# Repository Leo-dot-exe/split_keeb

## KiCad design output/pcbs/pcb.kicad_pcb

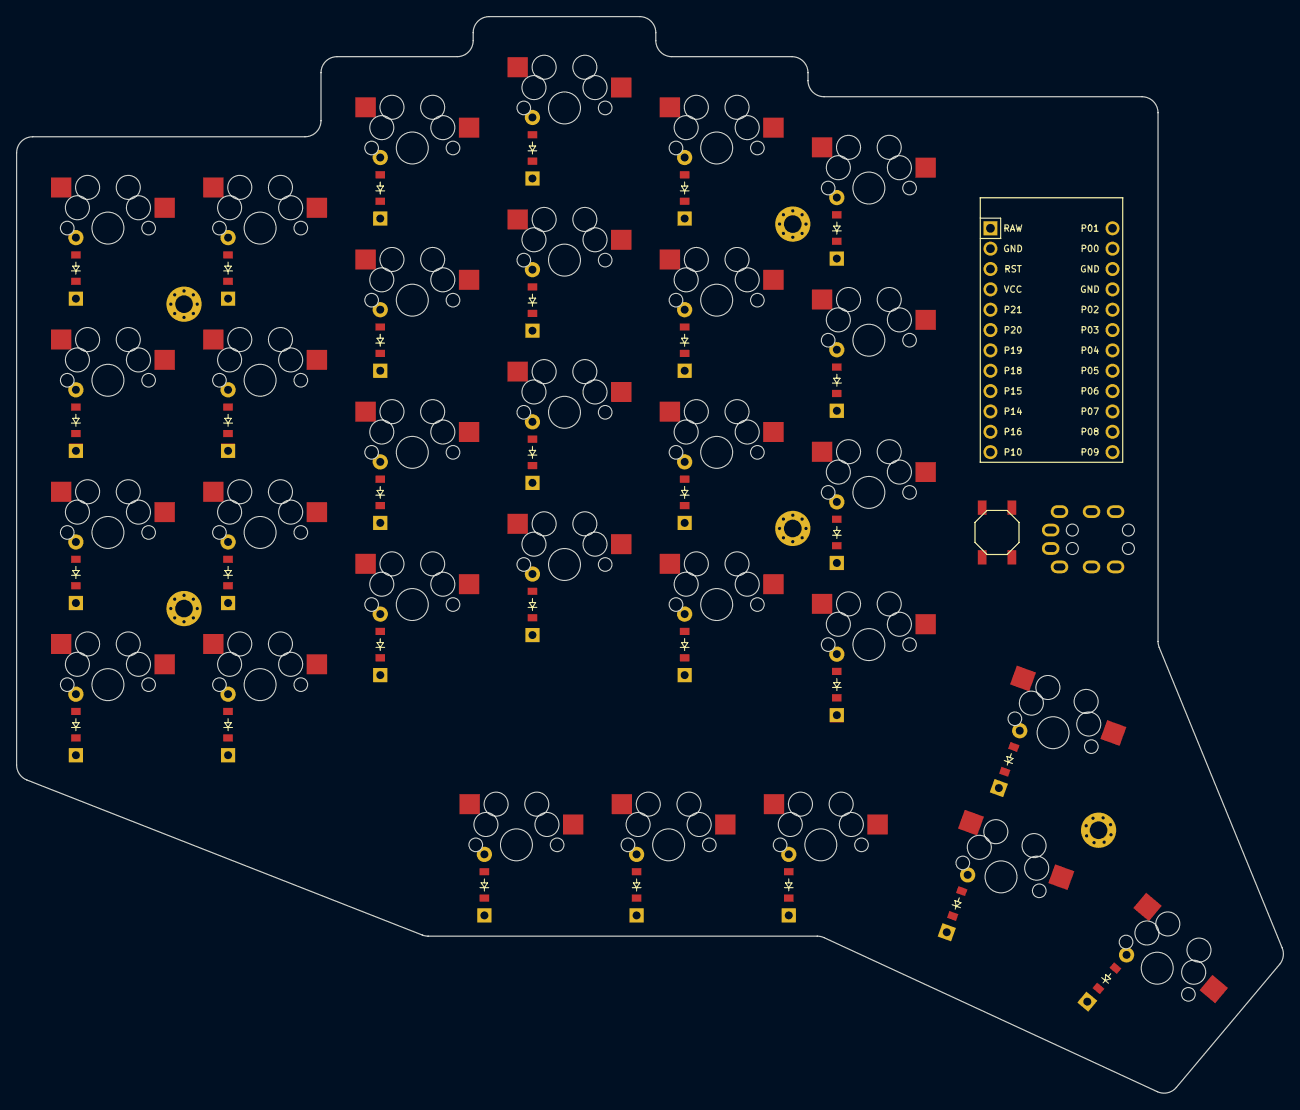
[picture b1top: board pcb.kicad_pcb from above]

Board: 2 copper layers, 158.2 x 134.4 mm, 68 parts (0 on the bottom side), 46 nets, no tracks yet.

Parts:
B1: SW_TACT_ALPS_SKQGABE010
D1, D2, D3, D4, D5, D6, D7, D8, D9, D10, D11, D12, D13, D14, D15, D16, D17, D18, D19, D20, D21, D22, D23, D24, D25, D26, D27, D28, D29, D30: ComboDiode
MCU1: ProMicro
S1, S2, S3, S4, S5, S6, S7, S8, S9, S10, S11, S12, S13, S14, S15, S16, S17, S18, S19, S20, S21, S22, S23, S24, S25, S26, S27, S28, S29, S30: MX
TRRS1: TRRS-PJ-320A-dual
_1, _2, _3, _4, _5: MountingHole_2.2mm_M2_Pad_Via

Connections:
GND: B1.1, MCU1.2, MCU1.15, MCU1.16, TRRS1.1
P0: MCU1.14, TRRS1.3
P1: MCU1.13, TRRS1.4
P7: MCU1.22, S21.1, S22.1, S23.1, S24.1, S30.1
P8: MCU1.23, S17.1, S18.1, S19.1, S20.1, S29.1
P9: MCU1.24, S13.1, S14.1, S15.1, S16.1, S28.1
P10: MCU1.12, S9.1, S10.1, S11.1, S12.1, S27.1
P14: MCU1.10, S1.1, S2.1, S3.1, S4.1, S25.1
P15: D25.1, D26.1, D27.1, D28.1, D29.1, D30.1, MCU1.9
P16: MCU1.11, S5.1, S6.1, S7.1, S8.1, S26.1
P18: D1.1, D5.1, D9.1, D13.1, D17.1, D21.1, MCU1.8
P19: D2.1, D6.1, D10.1, D14.1, D18.1, D22.1, MCU1.7
P20: D3.1, D7.1, D11.1, D15.1, D19.1, D23.1, MCU1.6
P21: D4.1, D8.1, D12.1, D16.1, D20.1, D24.1, MCU1.5
RST: B1.2, MCU1.3
VCC: MCU1.4, TRRS1.2
index_bottom: D17.2, S17.2
index_home: D18.2, S18.2
index_num: D20.2, S20.2
index_top: D19.2, S19.2
inner_bottom: D21.2, S21.2
inner_home: D22.2, S22.2
inner_num: D24.2, S24.2
inner_top: D23.2, S23.2
middle_bottom: D13.2, S13.2
middle_home: D14.2, S14.2
middle_num: D16.2, S16.2
middle_top: D15.2, S15.2
outer_bottom: D1.2, S1.2
outer_home: D2.2, S2.2
outer_num: D4.2, S4.2
outer_top: D3.2, S3.2
pinky_bottom: D5.2, S5.2
pinky_home: D6.2, S6.2
pinky_num: D8.2, S8.2
pinky_top: D7.2, S7.2
ring_bottom: D9.2, S9.2
ring_home: D10.2, S10.2
ring_num: D12.2, S12.2
ring_top: D11.2, S11.2
thumb0_thumb: D25.2, S25.2
thumb1_thumb: D26.2, S26.2
thumb2_thumb: D27.2, S27.2
thumb3_thumb: D28.2, S28.2
thumb4_thumb: D29.2, S29.2
thumb5_thumb: D30.2, S30.2

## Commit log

2025-08-07 working
2025-08-09 wired pcb
2025-08-09 read me
